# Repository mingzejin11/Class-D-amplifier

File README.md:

# Class-D-amplifier
Repo containing gerber files for crossover circuit and amplifier

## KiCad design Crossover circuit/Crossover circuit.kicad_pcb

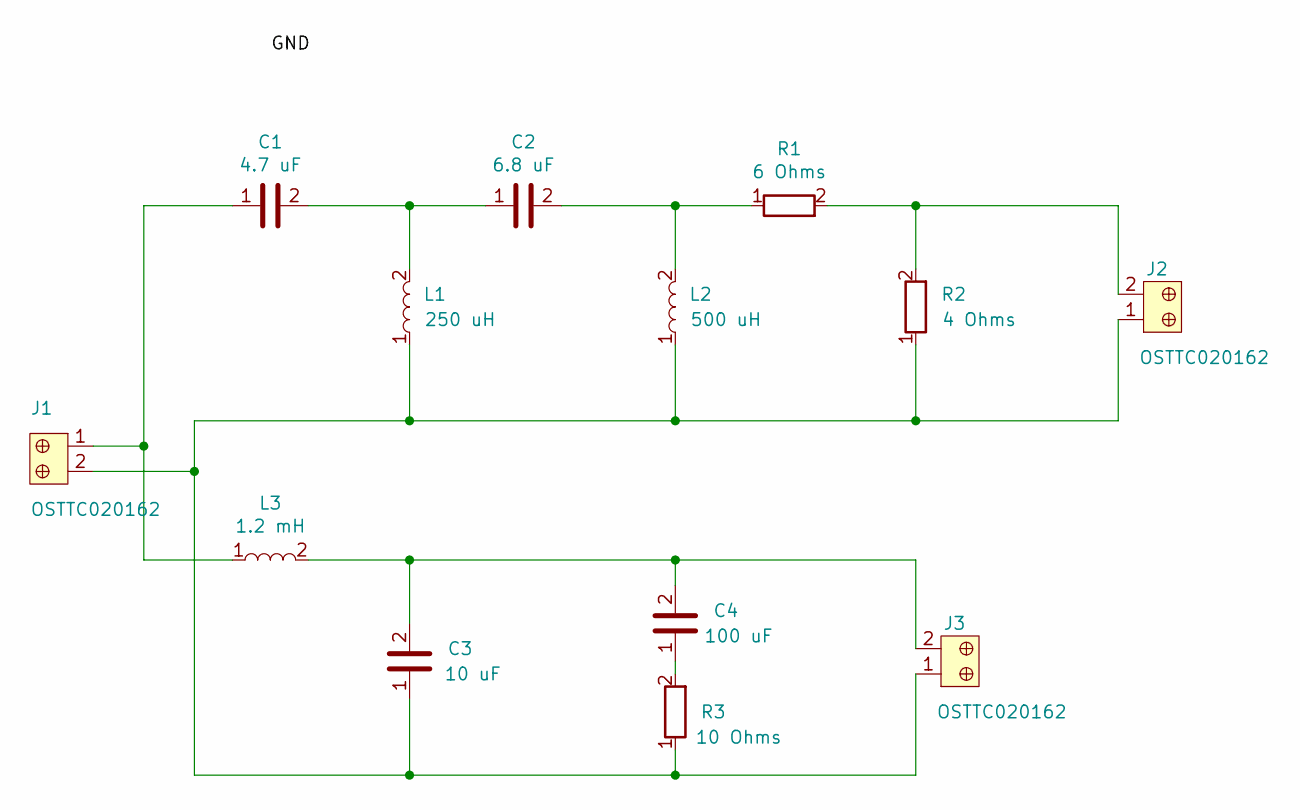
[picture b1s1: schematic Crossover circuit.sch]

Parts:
C1: 4.7 uF; 4.7 uF capacitor
C2: 6.8 uF; 6.8 uF capacitor
C3: 10 uF; 10 uF capacitor
C4: 100 uF; 100 uF capacitor
J1, J2, J3: OSTTC020162; Term_Block_1x2_P5mm; MPN OSTTC020162; Digi-Key_PN ED2600-ND
L1: 250 uH; 250 uH inductor
L2: 500 uH; 500 uH inductor
L3: 1.2 mH; 1.2 mH inductor
R1: 6 Ohms; Resistor
R2: 4 Ohms; Resistor
R3: 10 Ohms; Resistor

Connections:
unnamed: C1.1, J1.1, L3.1
unnamed: C1.2, C2.1, L1.2
unnamed: C2.2, L2.2, R1.1
unnamed: C3.1, J1.2, J2.1, J3.1, L1.1, L2.1, R2.1, R3.1
unnamed: C3.2, C4.2, J3.2, L3.2
unnamed: C4.1, R3.2
unnamed: J2.2, R1.2, R2.2

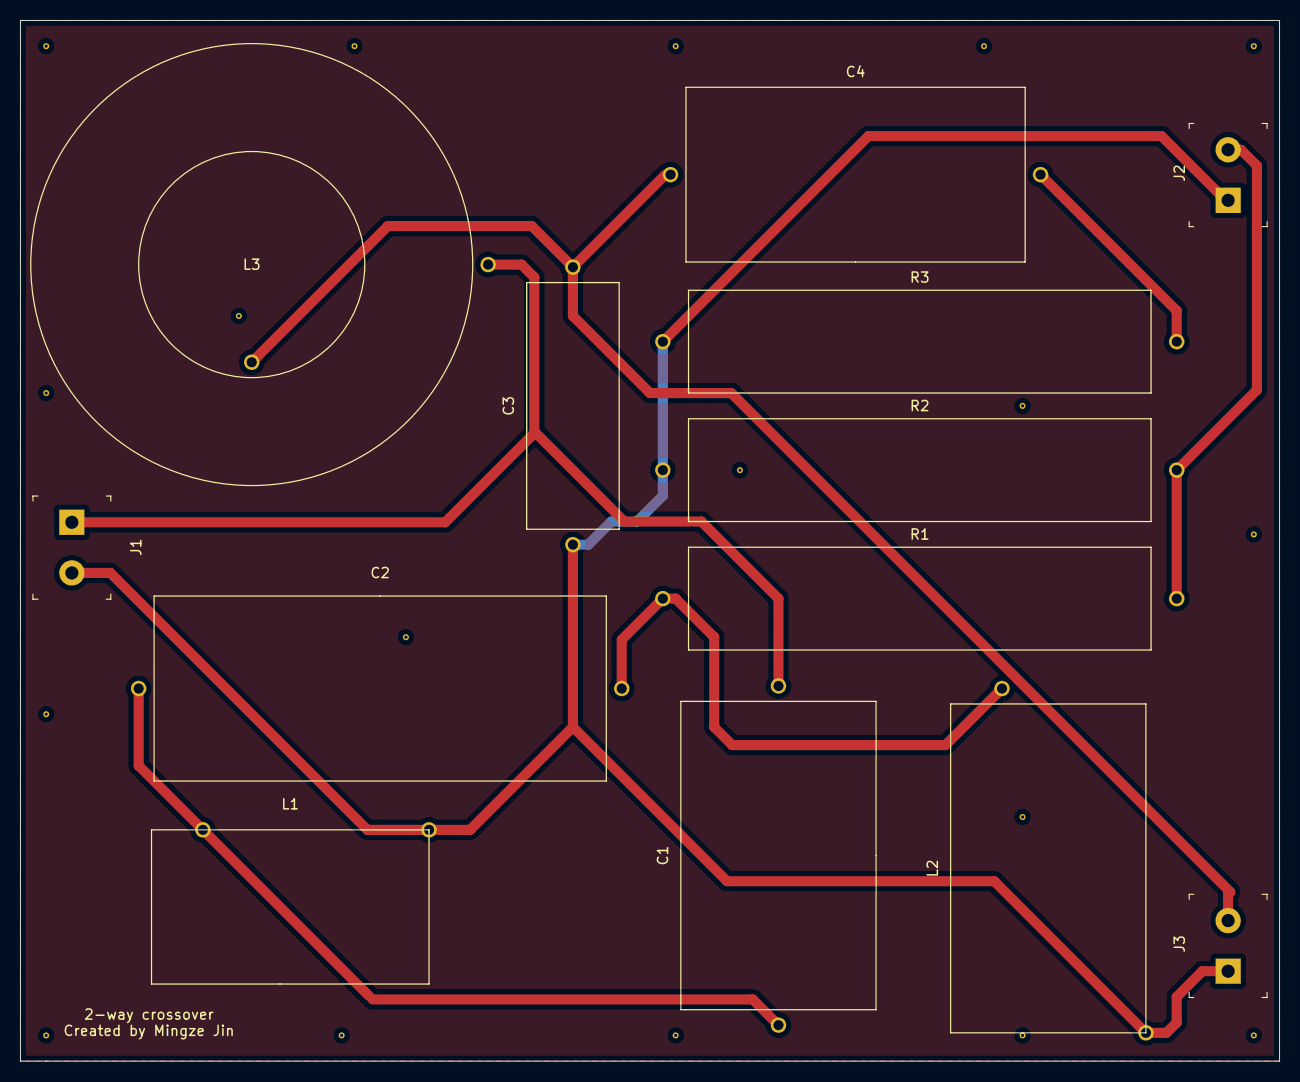
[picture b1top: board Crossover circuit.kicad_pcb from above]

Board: 2 copper layers, 124.5 x 102.9 mm, 13 parts (0 on the bottom side), 7 nets.

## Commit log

2020-05-13 adding crossover
2020-05-14 adding crossover gerber files
2020-05-14 adding gerber files
2020-05-14 updating crossover gerber files
2020-05-16 Fixed issue where L3 was flipped on the x-axis
2020-05-19 flipping an inductor's footprint
